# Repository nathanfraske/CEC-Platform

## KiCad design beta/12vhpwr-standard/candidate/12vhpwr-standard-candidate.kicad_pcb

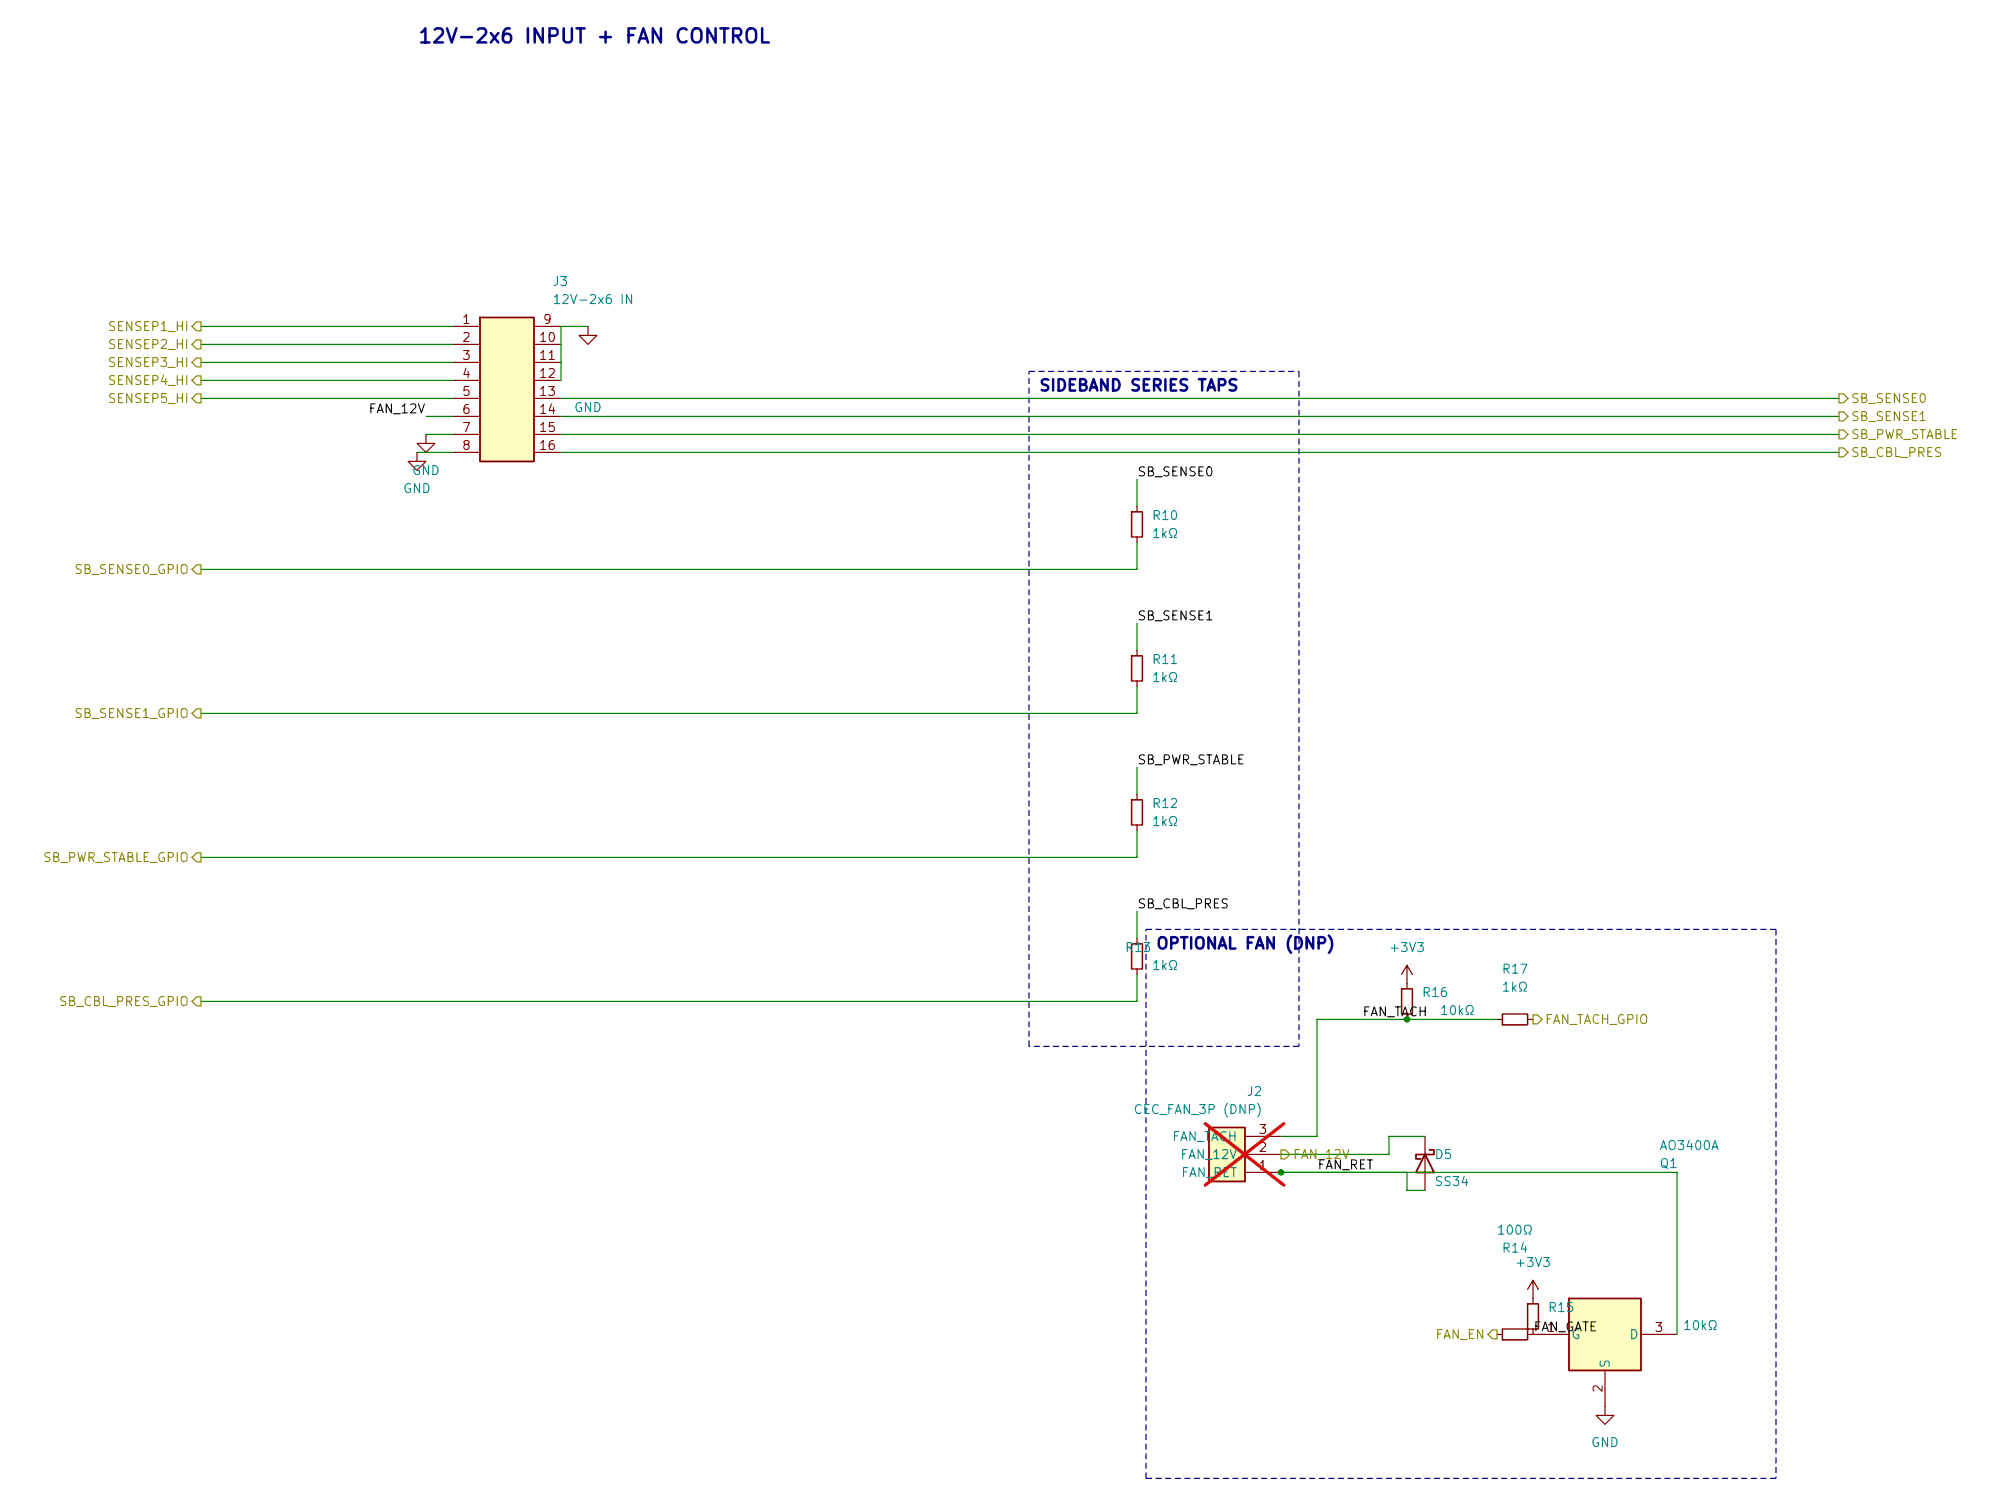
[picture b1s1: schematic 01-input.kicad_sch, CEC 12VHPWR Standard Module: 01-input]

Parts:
D5: SS34; D_SMA; MPN SS34; LCSC C8678
J2: CEC_FAN_3P (DNP); JST_PH_B3B-PH-K-S_1x03_P2.00mm_Vertical; MPN B3B-PH-K-S(LF)(SN); LCSC C131339; not fitted
J3: 12V-2x6 IN; CEC_12V2x6_Horizontal; MPN 2191161161; JLCPCB consigned (not in JLC catalog)
Q1: AO3400A; SOT-23-3_L2.9-W1.3-P1.90-LS2.4-BR; MPN AO3400A; LCSC C20917
R10, R11, R12, R13, R17: 1kΩ; R_0402_1005Metric; MPN 0402WGF1001TCE; LCSC C11702
R14: 100Ω; R_0402_1005Metric; MPN RC0402JR-07100RL; LCSC C106233
R15, R16: 10kΩ; R_0402_1005Metric; MPN 0402WGF1002TCE; LCSC C25744

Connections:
/FAN_12V: D5.1 (K), J2.2 (FAN_12V), J3.6 (+12V); also elsewhere on the board
/FAN_EN: R14.1; also elsewhere on the board
/SB_CBL_PRES: J3.16 (SENSE), R13.1; also elsewhere on the board
/SB_CBL_PRES_GPIO: R13.2; also elsewhere on the board
/SB_PWR_STABLE: J3.15 (SENSE), R12.1; also elsewhere on the board
/SB_PWR_STABLE_GPIO: R12.2; also elsewhere on the board
/SB_SENSE0: J3.13 (SENSE), R10.1; also elsewhere on the board
/SB_SENSE0_GPIO: R10.2; also elsewhere on the board
/SB_SENSE1: J3.14 (SENSE), R11.1; also elsewhere on the board
/SB_SENSE1_GPIO: R11.2; also elsewhere on the board
/SENSEP1_HI: J3.1 (+12V); also elsewhere on the board
/SENSEP2_HI: J3.2 (+12V); also elsewhere on the board
/SENSEP3_HI: J3.3 (+12V); also elsewhere on the board
/SENSEP4_HI: J3.4 (+12V); also elsewhere on the board
/SENSEP5_HI: J3.5 (+12V); also elsewhere on the board

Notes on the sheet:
12V-2x6 INPUT + FAN CONTROL
SIDEBAND SERIES TAPS
OPTIONAL FAN (DNP)

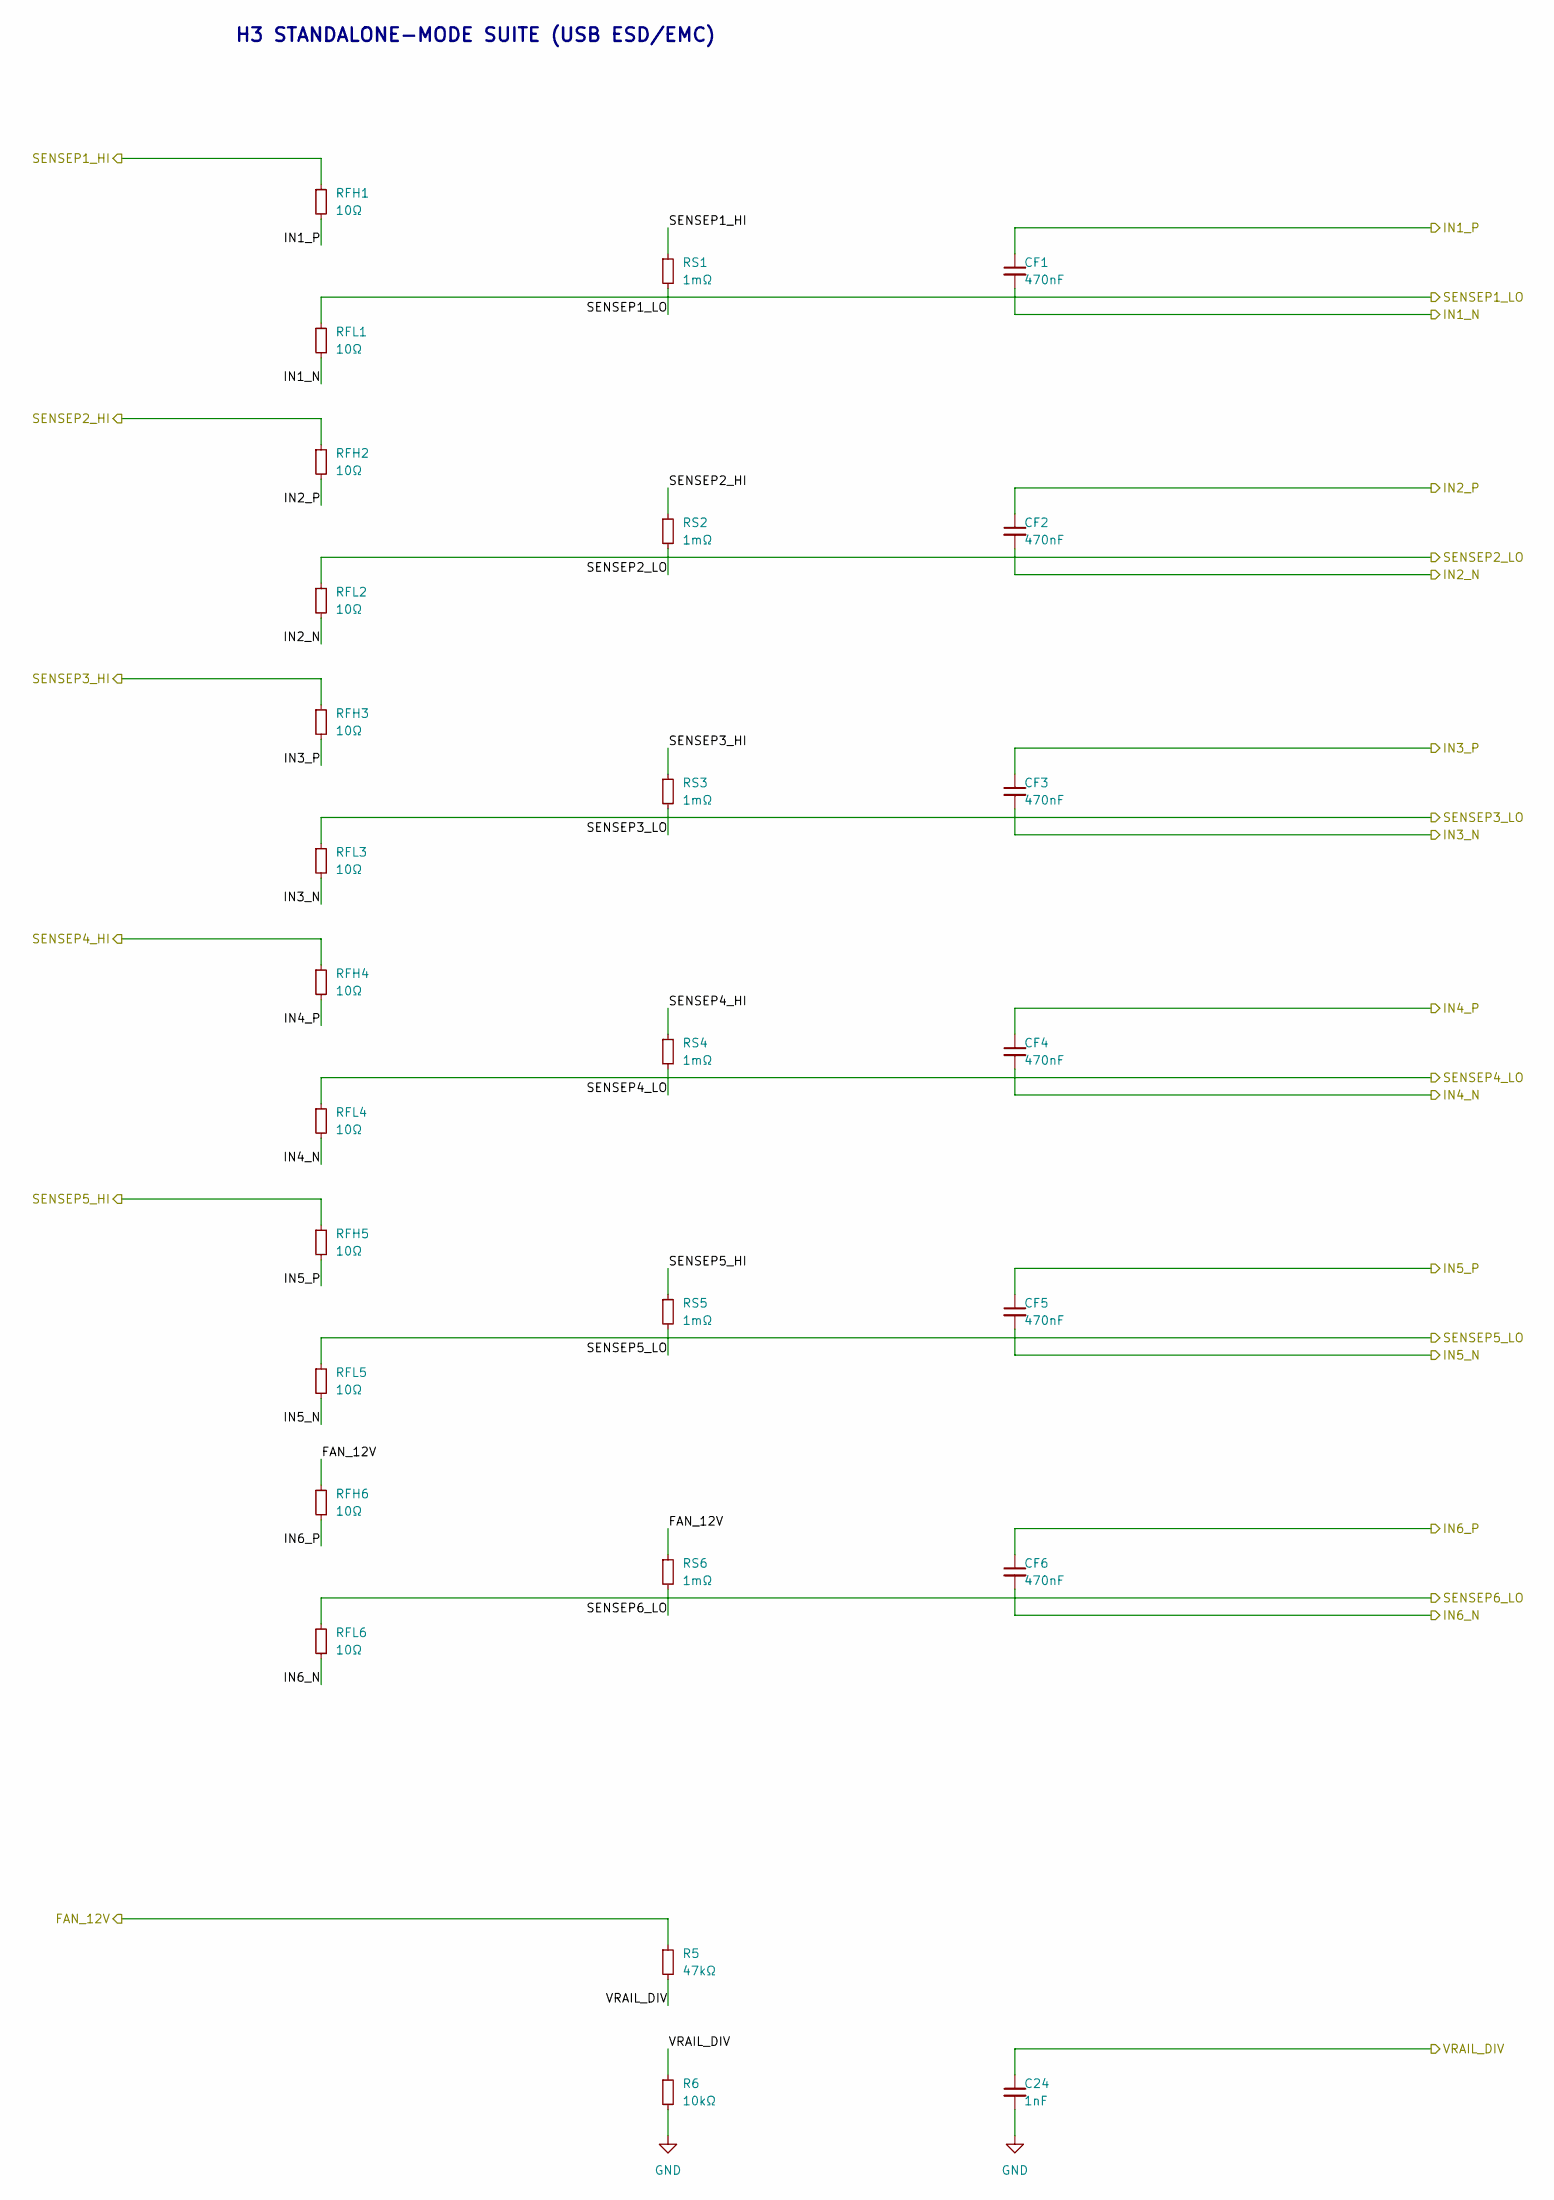
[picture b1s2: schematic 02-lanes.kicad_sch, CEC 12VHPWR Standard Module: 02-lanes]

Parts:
C24: 1nF; C_0402_1005Metric; MPN GRM1555C1H102JA01D; LCSC C76947
CF1, CF2, CF3, CF4, CF5, CF6: 470nF; C_0603_1608Metric; MPN CL10B474KA8NNNC; LCSC C1623
R5: 47kΩ; R_0402_1005Metric; Tolerance 0.1%; MPN RT0402BRD0747KL; LCSC C728561
R6: 10kΩ; R_0402_1005Metric; Tolerance 0.1%; MPN RT0402BRD0710KL; LCSC C190095
RFH1, RFH2, RFH3, RFH4, RFH5, RFH6: 10Ω; R_0402_1005Metric; Tolerance 0.1%; MPN RT0402BRE0710RL; LCSC C705642
RFL1, RFL2, RFL3, RFL4, RFL5, RFL6: 10Ω; R_0402_1005Metric; Tolerance 0.1%; MPN RT0402BRE0710RL; LCSC C705642
RS1, RS2, RS3, RS4, RS5, RS6: 1mΩ; R_2512_6332Metric; MPN CSS2H-2512R-1L00F; LCSC C4175647

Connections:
/FAN_12V: R5.1, RFH6.1, RS6.1; also elsewhere on the board
/IN1_N: CF1.2, RFL1.2; also elsewhere on the board
/IN1_P: CF1.1, RFH1.2; also elsewhere on the board
/IN2_N: CF2.2, RFL2.2; also elsewhere on the board
/IN2_P: CF2.1, RFH2.2; also elsewhere on the board
/IN3_N: CF3.2, RFL3.2; also elsewhere on the board
/IN3_P: CF3.1, RFH3.2; also elsewhere on the board
/IN4_N: CF4.2, RFL4.2; also elsewhere on the board
/IN4_P: CF4.1, RFH4.2; also elsewhere on the board
/IN5_N: CF5.2, RFL5.2; also elsewhere on the board
/IN5_P: CF5.1, RFH5.2; also elsewhere on the board
/IN6_N: CF6.2, RFL6.2; also elsewhere on the board
/IN6_P: CF6.1, RFH6.2; also elsewhere on the board
/SENSEP1_HI: RFH1.1, RS1.1; also elsewhere on the board
/SENSEP1_LO: RFL1.1, RS1.2; also elsewhere on the board
/SENSEP2_HI: RFH2.1, RS2.1; also elsewhere on the board
/SENSEP2_LO: RFL2.1, RS2.2; also elsewhere on the board
/SENSEP3_HI: RFH3.1, RS3.1; also elsewhere on the board
/SENSEP3_LO: RFL3.1, RS3.2; also elsewhere on the board
/SENSEP4_HI: RFH4.1, RS4.1; also elsewhere on the board
/SENSEP4_LO: RFL4.1, RS4.2; also elsewhere on the board
/SENSEP5_HI: RFH5.1, RS5.1; also elsewhere on the board
/SENSEP5_LO: RFL5.1, RS5.2; also elsewhere on the board
/SENSEP6_LO: RFL6.1, RS6.2; also elsewhere on the board
/VRAIL_DIV: C24.1, R5.2, R6.1; also elsewhere on the board

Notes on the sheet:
H3 STANDALONE-MODE SUITE (USB ESD/EMC)

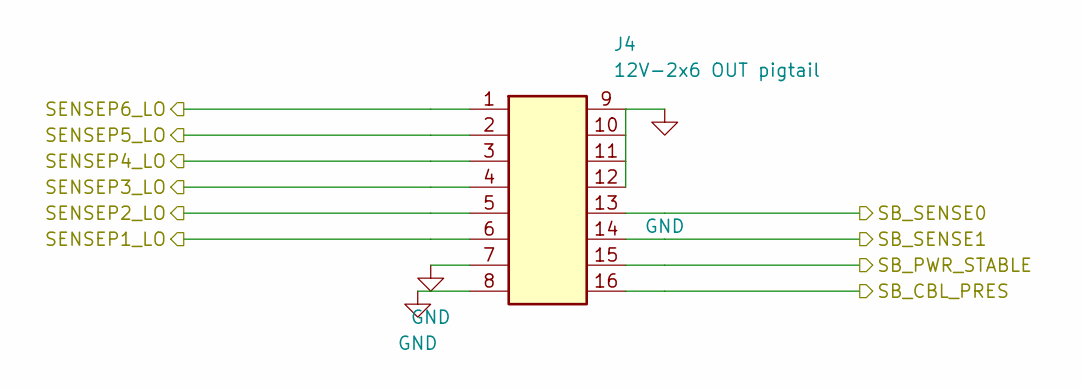
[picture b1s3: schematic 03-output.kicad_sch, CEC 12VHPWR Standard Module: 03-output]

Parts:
J4: 12V-2x6 OUT pigtail; CEC_12V2x6_Horizontal; MPN 2191161161; JLCPCB consigned (not in JLC catalog)

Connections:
/SB_CBL_PRES: J4.16 (SENSE); also elsewhere on the board
/SB_PWR_STABLE: J4.15 (SENSE); also elsewhere on the board
/SB_SENSE0: J4.13 (SENSE); also elsewhere on the board
/SB_SENSE1: J4.14 (SENSE); also elsewhere on the board
/SENSEP1_LO: J4.6 (+12V); also elsewhere on the board
/SENSEP2_LO: J4.5 (+12V); also elsewhere on the board
/SENSEP3_LO: J4.4 (+12V); also elsewhere on the board
/SENSEP4_LO: J4.3 (+12V); also elsewhere on the board
/SENSEP5_LO: J4.2 (+12V); also elsewhere on the board
/SENSEP6_LO: J4.1 (+12V); also elsewhere on the board

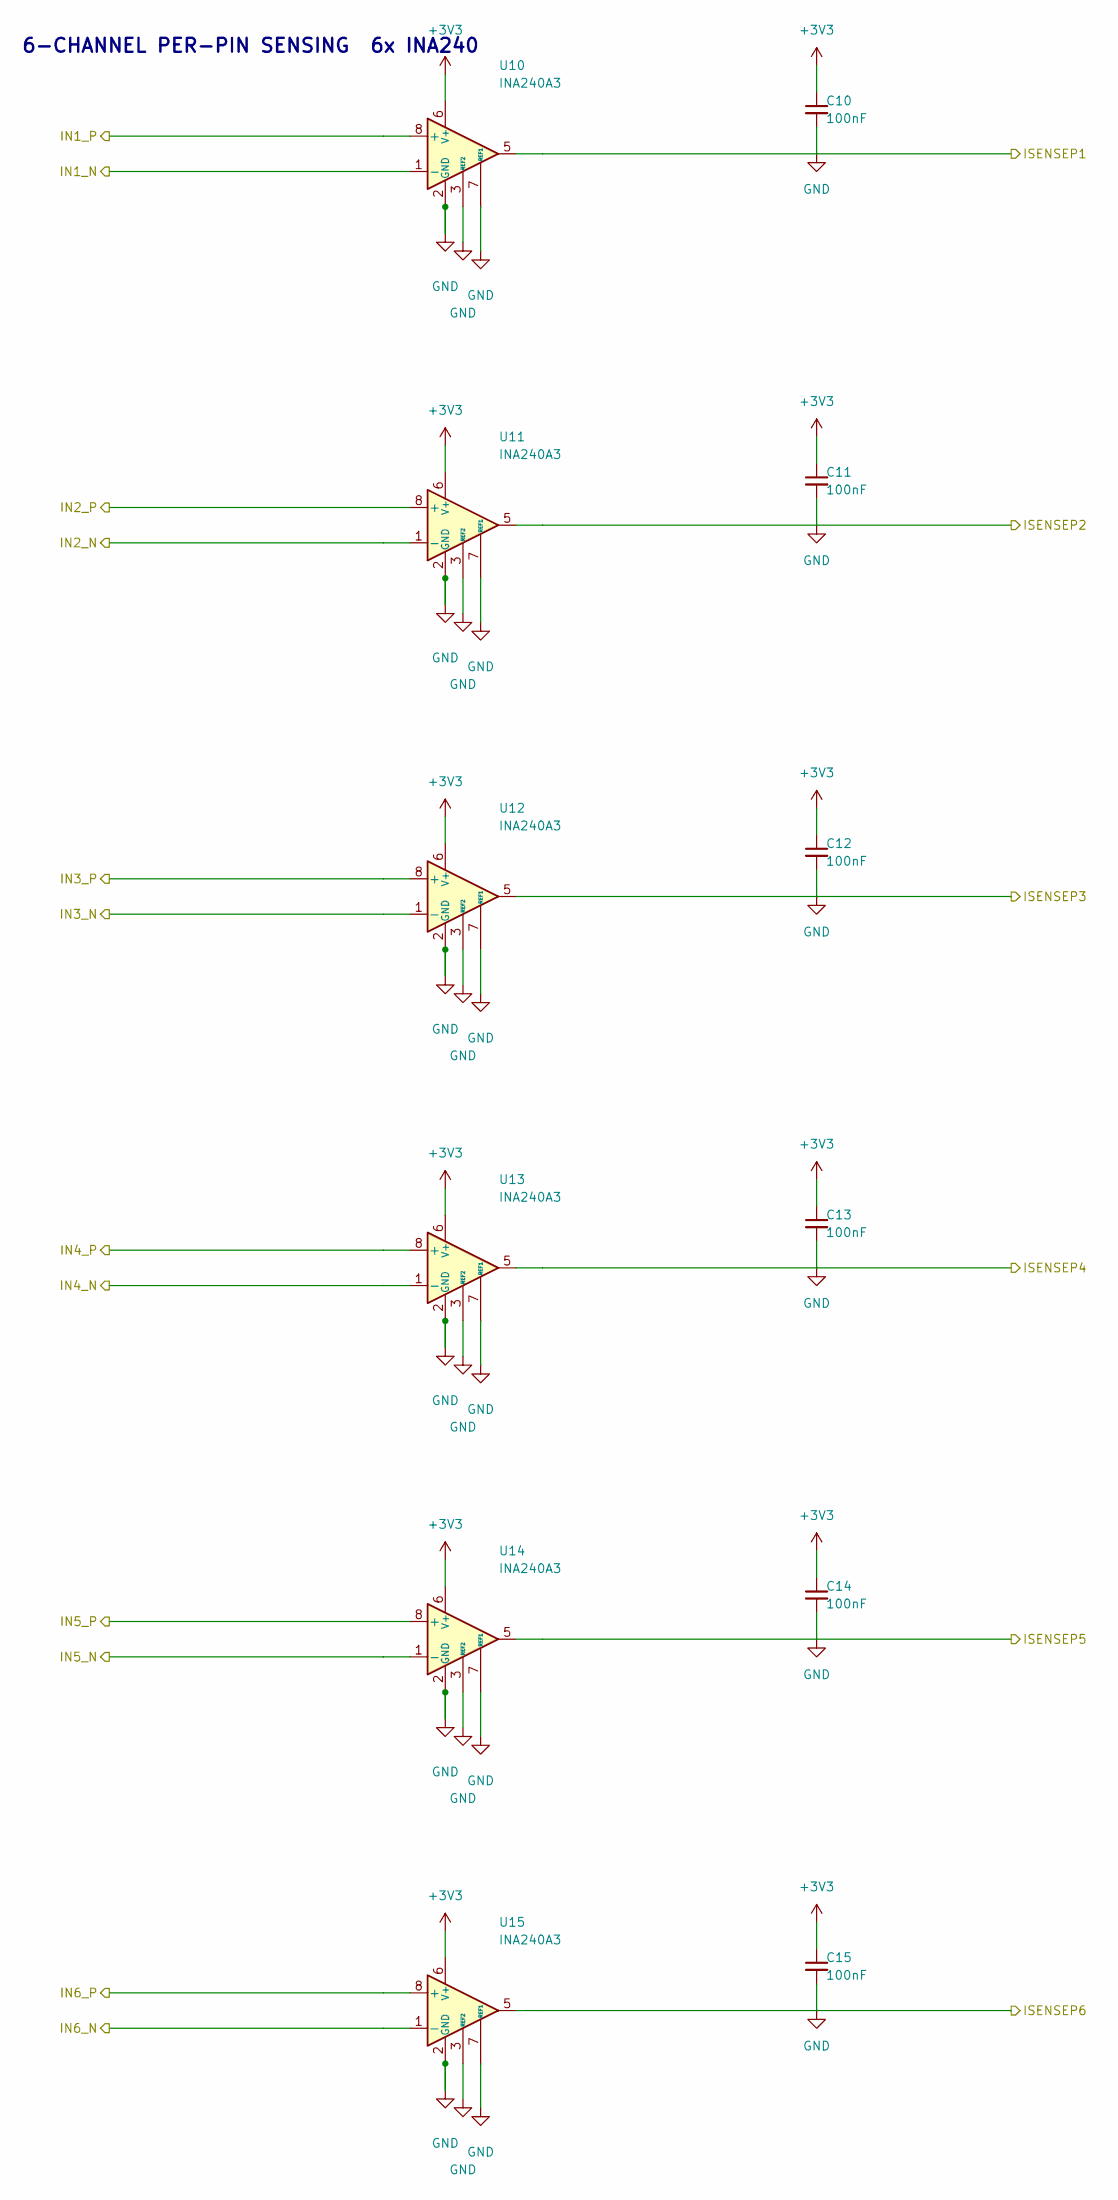
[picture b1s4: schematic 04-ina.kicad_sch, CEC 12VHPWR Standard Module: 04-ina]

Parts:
C10, C11, C12, C13, C14, C15: 100nF; C_0402_1005Metric; MPN CL05B104KO5NNNC; LCSC C1525
U10, U11, U12, U13, U14, U15: INA240A3; SOIC-8_3.9x4.9mm_P1.27mm; MPN INA240A3DR; LCSC C2060584

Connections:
/IN1_N: U10.1 (-); also elsewhere on the board
/IN1_P: U10.8 (+); also elsewhere on the board
/IN2_N: U11.1 (-); also elsewhere on the board
/IN2_P: U11.8 (+); also elsewhere on the board
/IN3_N: U12.1 (-); also elsewhere on the board
/IN3_P: U12.8 (+); also elsewhere on the board
/IN4_N: U13.1 (-); also elsewhere on the board
/IN4_P: U13.8 (+); also elsewhere on the board
/IN5_N: U14.1 (-); also elsewhere on the board
/IN5_P: U14.8 (+); also elsewhere on the board
/IN6_N: U15.1 (-); also elsewhere on the board
/IN6_P: U15.8 (+); also elsewhere on the board

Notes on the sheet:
6-CHANNEL PER-PIN SENSING 6x INA240

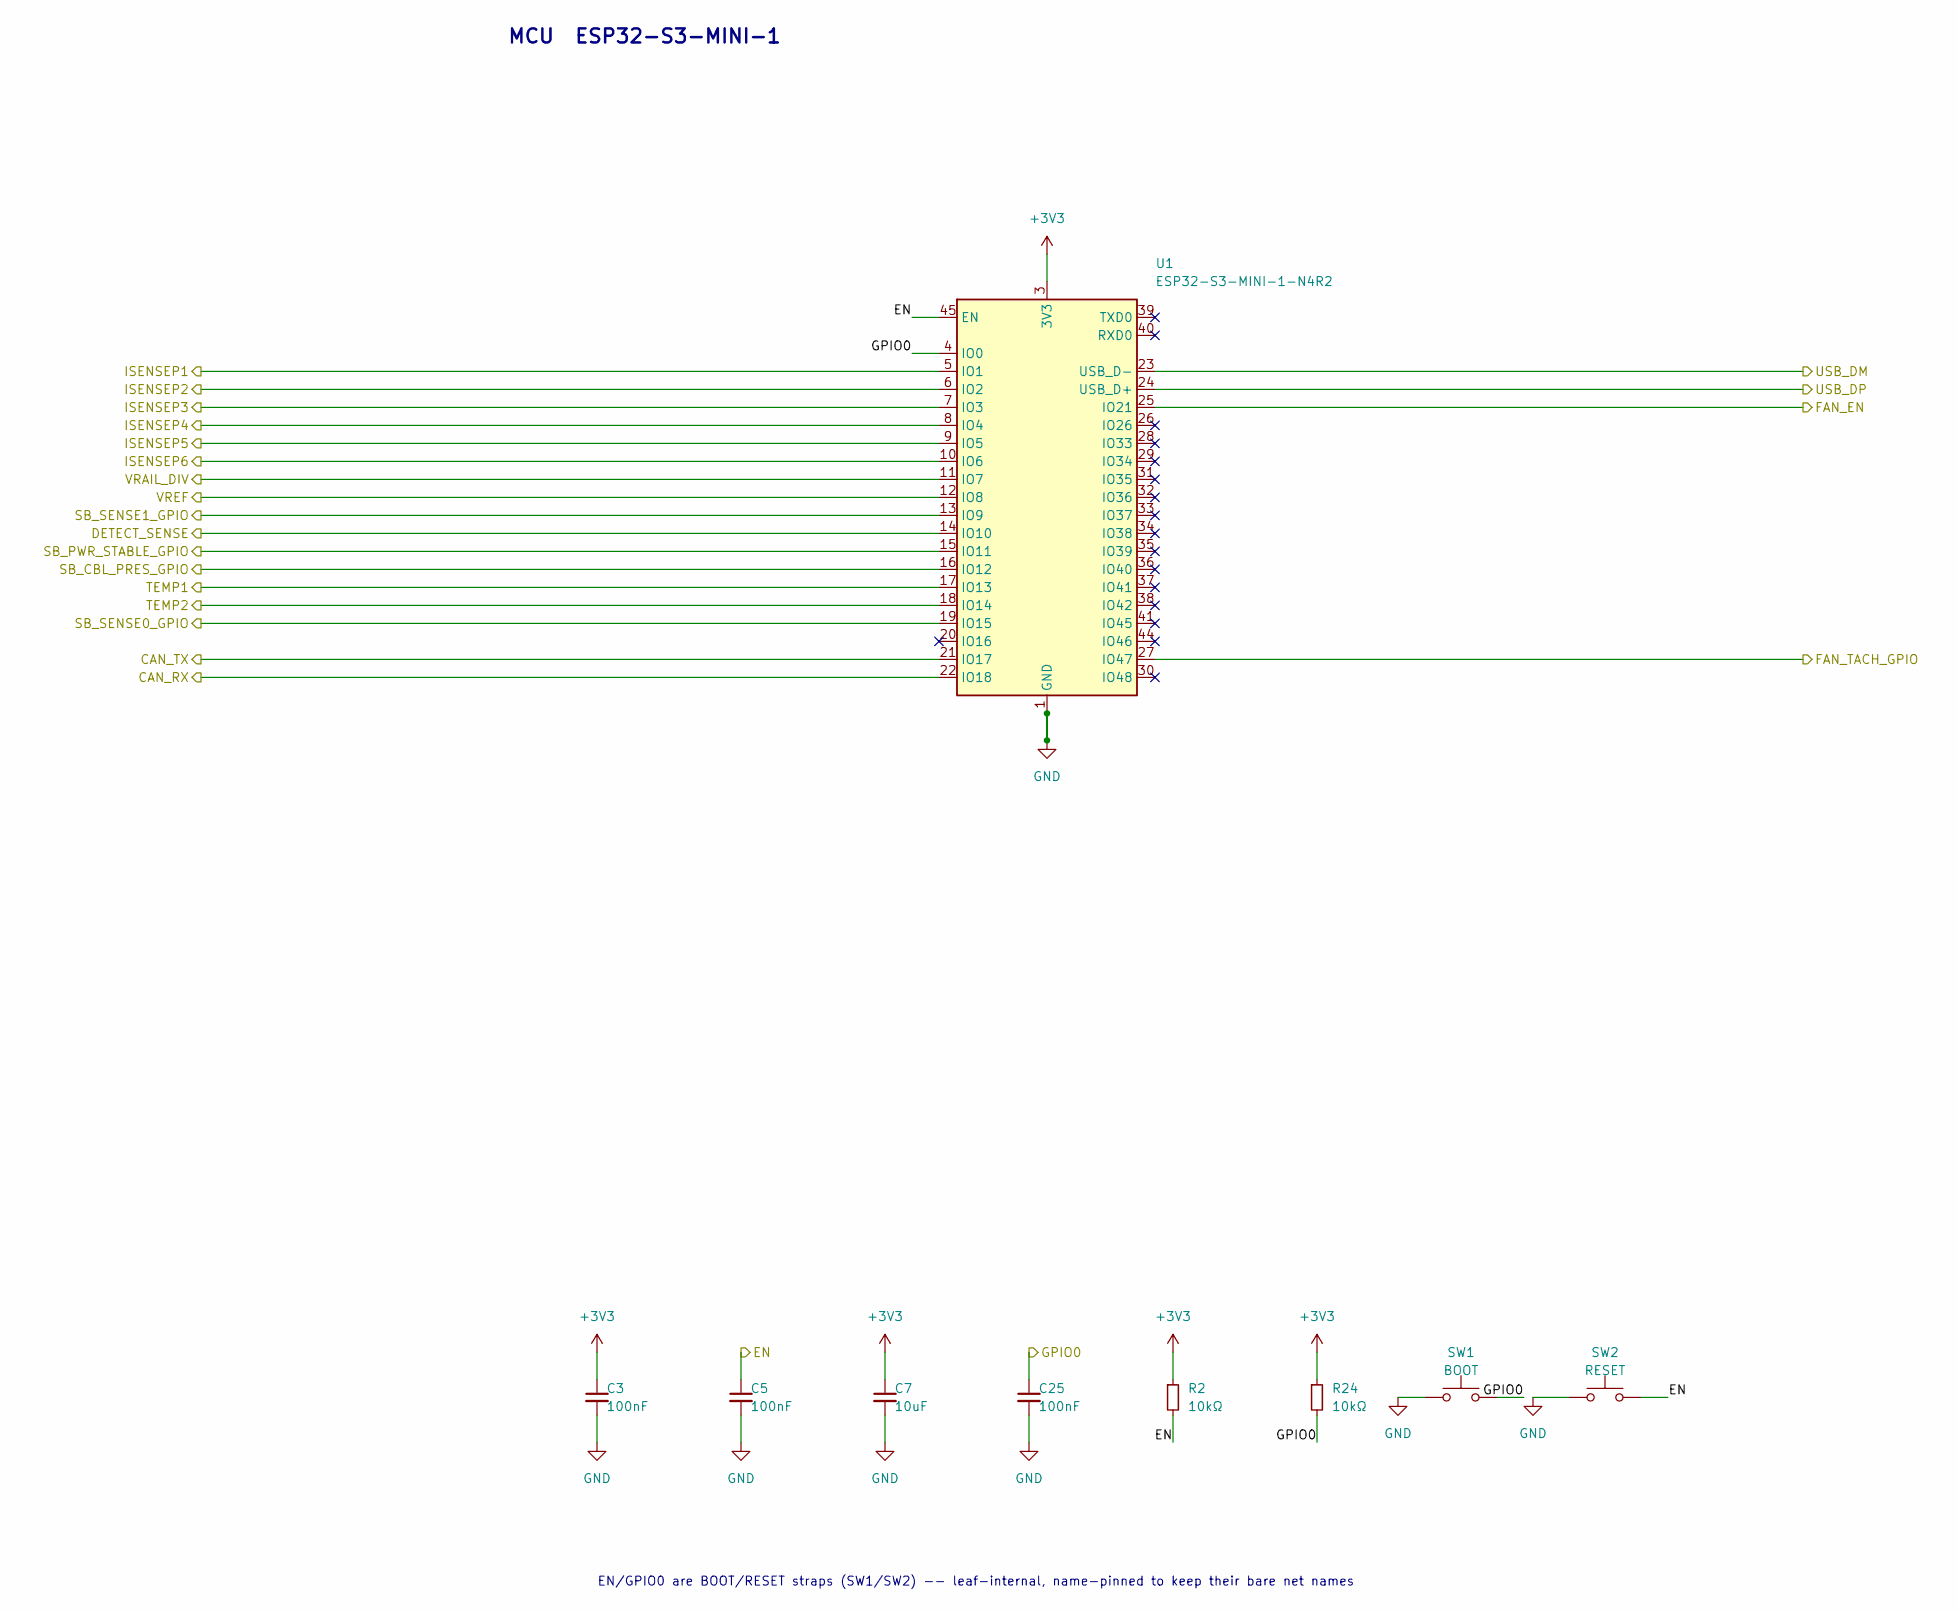
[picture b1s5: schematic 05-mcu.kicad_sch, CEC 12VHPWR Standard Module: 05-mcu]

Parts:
C3, C5, C25: 100nF; C_0402_1005Metric; MPN CL05B104KO5NNNC; LCSC C1525
C7: 10uF; C_0805_2012Metric; MPN CL21A106KAYNNNE; LCSC C15850
R2, R24: 10kΩ; R_0402_1005Metric; MPN 0402WGF1002TCE; LCSC C25744
SW1: BOOT; TS-1088-AR02016; MPN TS-1088-AR02016; LCSC C720477
SW2: RESET; TS-1088-AR02016; MPN TS-1088-AR02016; LCSC C720477
U1: ESP32-S3-MINI-1-N4R2; ESP32-S2-MINI-1_NoAntKeepout; MPN ESP32-S3-MINI-1-N4R2; LCSC C3013941

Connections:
/CAN_RX: U1.22 (IO18); also elsewhere on the board
/CAN_TX: U1.21 (IO17); also elsewhere on the board
/EN: C5.1, R2.2, SW2.2, U1.45 (EN)
/FAN_EN: U1.25 (IO21); also elsewhere on the board
/GPIO0: C25.1, R24.2, SW1.2, U1.4 (IO0)
/SB_CBL_PRES_GPIO: U1.16 (IO12); also elsewhere on the board
/SB_PWR_STABLE_GPIO: U1.15 (IO11); also elsewhere on the board
/SB_SENSE0_GPIO: U1.19 (IO15); also elsewhere on the board
/SB_SENSE1_GPIO: U1.13 (IO9); also elsewhere on the board
/TEMP1: U1.17 (IO13); also elsewhere on the board
/TEMP2: U1.18 (IO14); also elsewhere on the board
/USB_DM: U1.23 (USB_D-); also elsewhere on the board
/USB_DP: U1.24 (USB_D+); also elsewhere on the board
/VRAIL_DIV: U1.11 (IO7); also elsewhere on the board
/VREF: U1.12 (IO8); also elsewhere on the board

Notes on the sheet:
MCU ESP32-S3-MINI-1
EN/GPIO0 are BOOT/RESET straps (SW1/SW2) -- leaf-internal, name-pinned to keep their bare net names

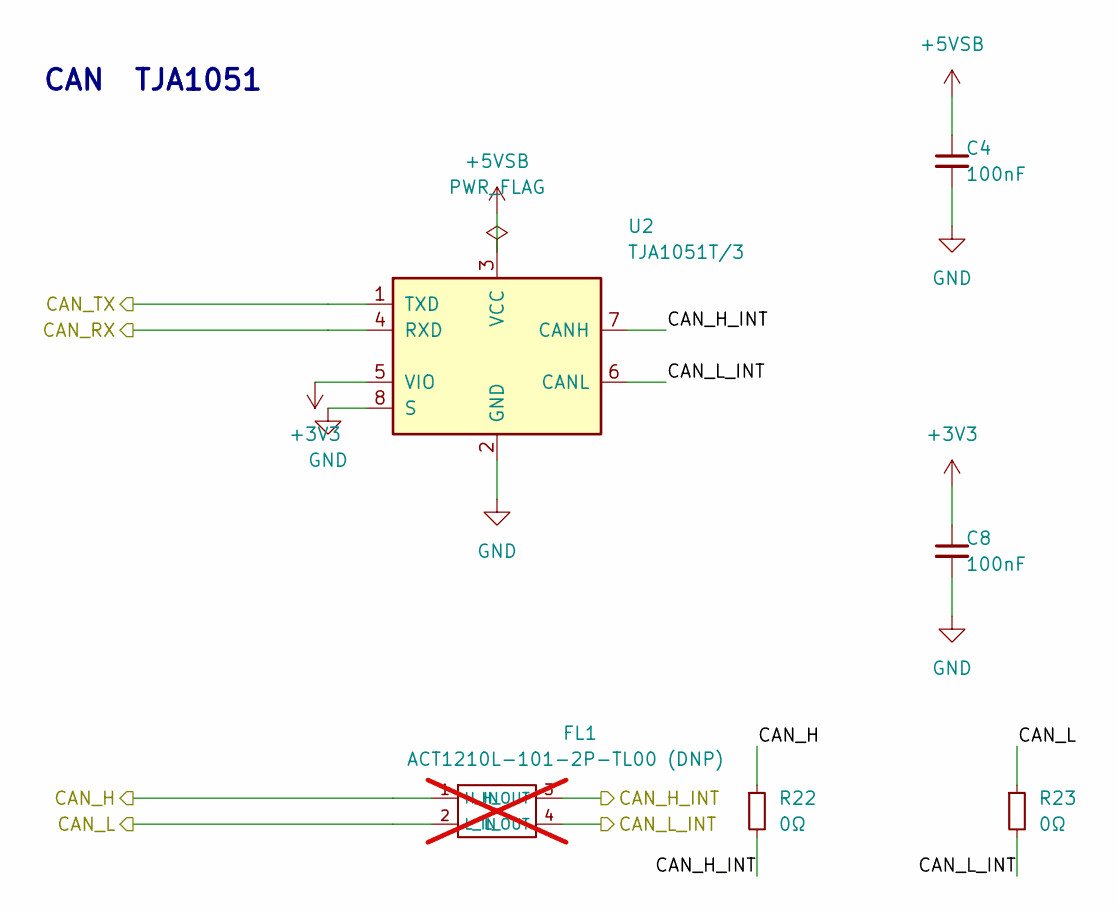
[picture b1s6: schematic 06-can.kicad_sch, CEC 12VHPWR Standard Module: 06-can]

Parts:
C4, C8: 100nF; C_0402_1005Metric; MPN CL05B104KO5NNNC; LCSC C1525
FL1: ACT1210L-101-2P-TL00 (DNP); MPN ACT1210L-101-2P-TL00; LCSC C307643; not fitted
R22, R23: 0Ω; R_0402_1005Metric; MPN 0402WGF0000TCE; LCSC C17168
U2: TJA1051T/3; SOIC-8_3.9x4.9mm_P1.27mm; MPN TJA1051T/3/1J; LCSC C38695

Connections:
+5VSB: C4.1, U2.3 (VCC); also elsewhere on the board
/CAN_H: R22.1; also elsewhere on the board
/CAN_H_INT: R22.2, U2.7 (CANH)
/CAN_L: R23.1; also elsewhere on the board
/CAN_L_INT: R23.2, U2.6 (CANL)
/CAN_RX: U2.4 (RXD); also elsewhere on the board
/CAN_TX: U2.1 (TXD); also elsewhere on the board

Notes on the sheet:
CAN TJA1051

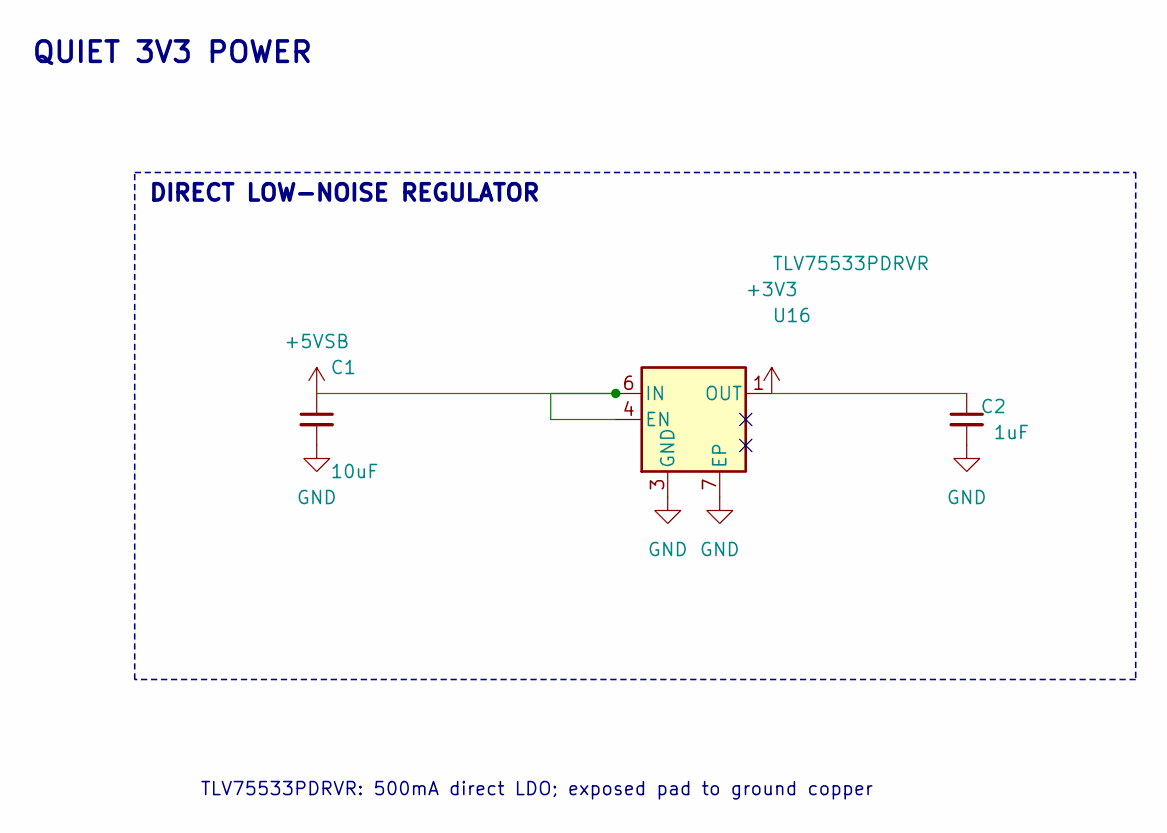
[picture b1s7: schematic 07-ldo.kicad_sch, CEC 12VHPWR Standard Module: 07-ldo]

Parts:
C1: 10uF; C_0603_1608Metric; MPN CL10A106MA8NRNC; LCSC C96446
C2: 1uF; C_0603_1608Metric; MPN CL10B105KA8NNNC; LCSC C29936
U16: TLV75533PDRVR; WSON-6-1EP_2x2mm_P0.65mm_EP1x1.6mm; MPN TLV75533PDRVR; LCSC C2861750

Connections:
+5VSB: C1.1, U16.4 (EN), U16.6 (IN); also elsewhere on the board

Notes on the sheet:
QUIET 3V3 POWER
TLV75533PDRVR: 500mA direct LDO; exposed pad to ground copper
DIRECT LOW-NOISE REGULATOR

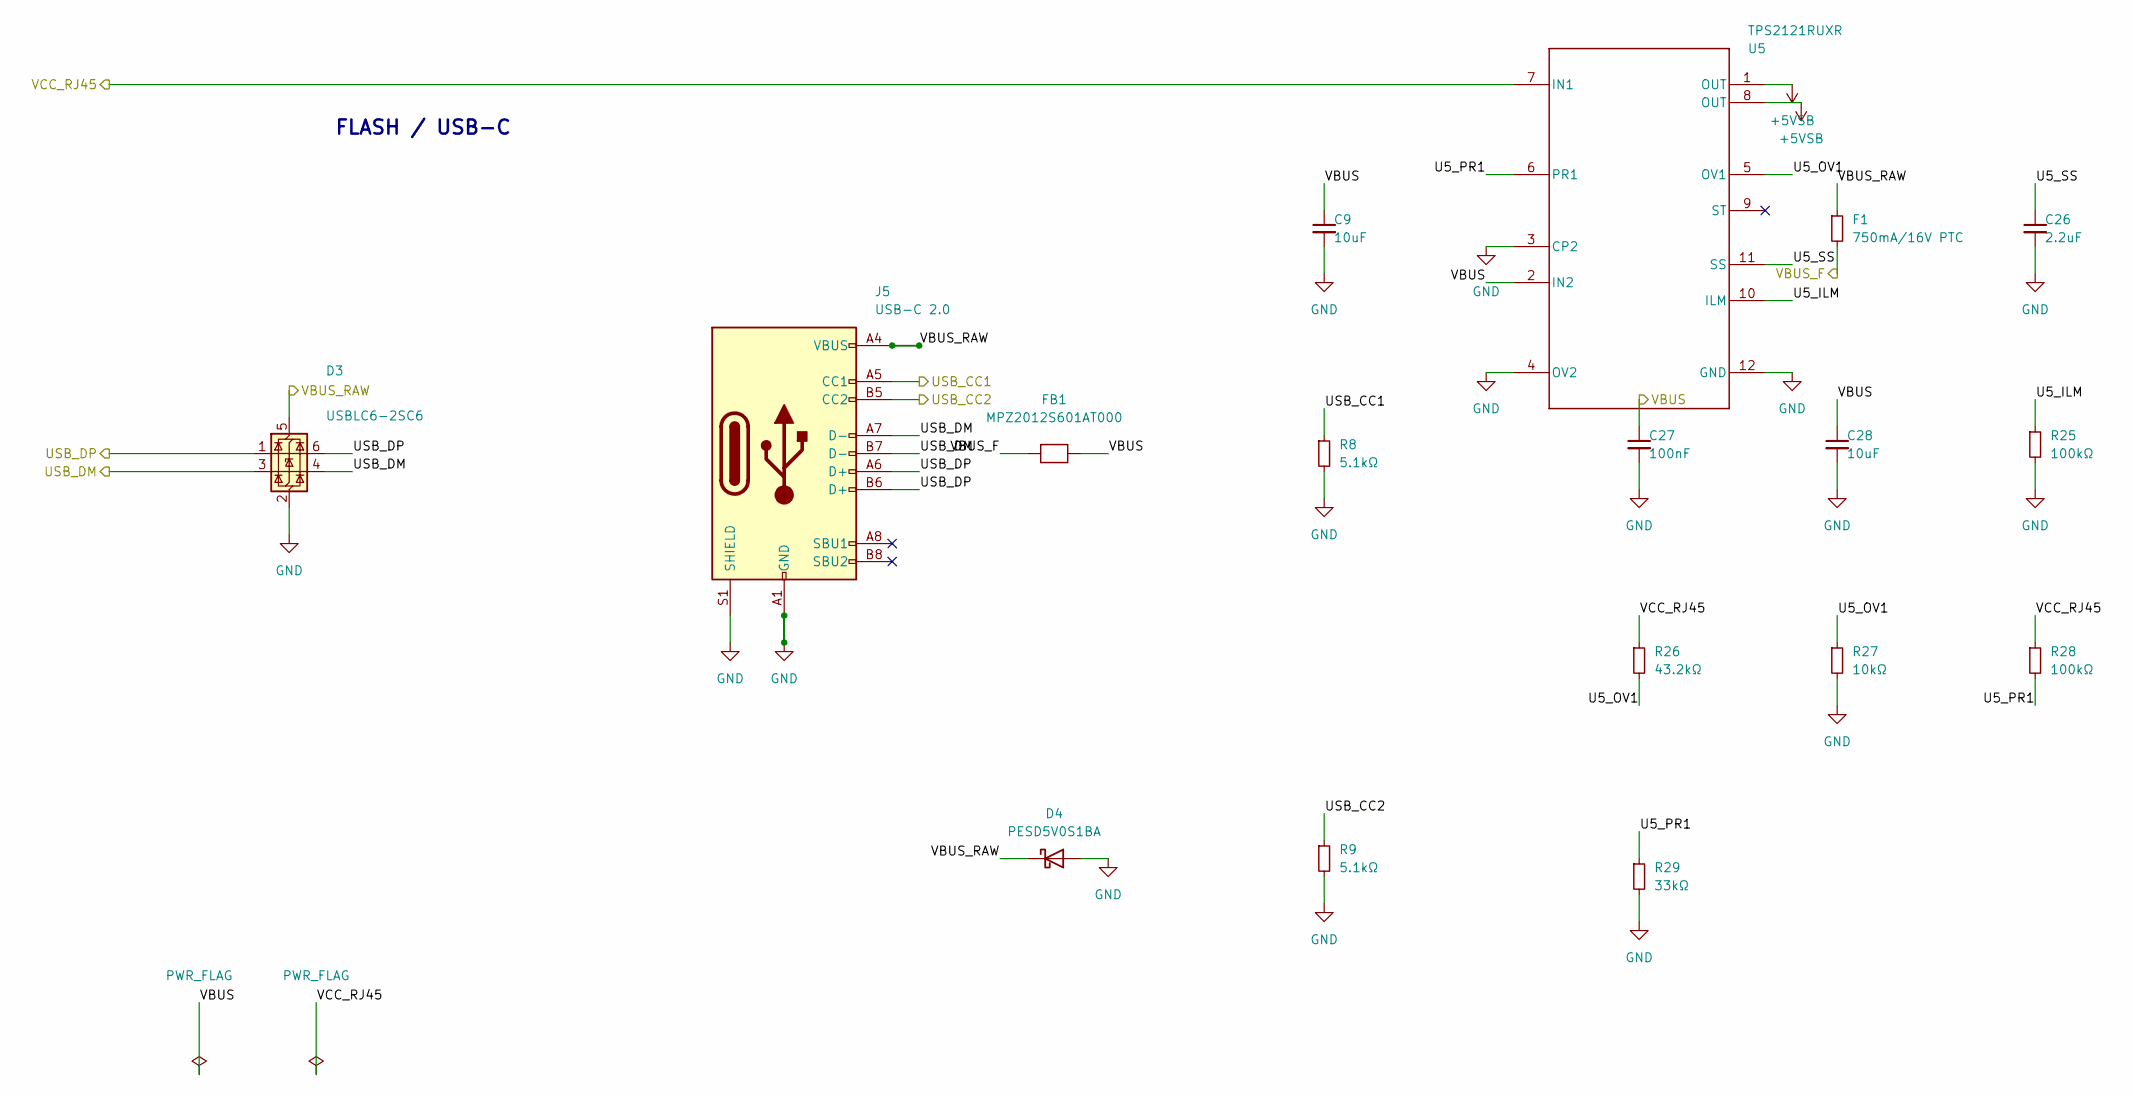
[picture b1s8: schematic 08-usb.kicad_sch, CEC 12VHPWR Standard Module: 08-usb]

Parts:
C9, C28: 10uF; C_0805_2012Metric; MPN CL21A106KAYNNNE; LCSC C15850
C26: 2.2uF; C_0603_1608Metric; MPN CL10A225KO8NNNC; LCSC C23630
C27: 100nF; C_0402_1005Metric; MPN CL05B104KO5NNNC; LCSC C1525
D3: USBLC6-2SC6; SOT-23-6; MPN USBLC6-2SC6; LCSC C2687116
D4: PESD5V0S1BA; D_SOD-323; MPN PESD5V0S1BA; LCSC C5261083
F1: 750mA/16V PTC; R_1206_3216Metric; MPN 1206L075/16WR; LCSC C371166
FB1: MPZ2012S601AT000; C_0805_2012Metric; MPN MPZ2012S601AT000; LCSC C21519
J5: USB-C 2.0; USB_C_Receptacle_XKB_U262-16XN-4BVC11; MPN U262-161N-4BVC11; LCSC C319148
R8, R9: 5.1kΩ; R_0402_1005Metric; MPN 0402WGF5101TCE; LCSC C25905
R25, R28: 100kΩ; R_0402_1005Metric; MPN 0402WGF1003TCE; LCSC C25741
R26: 43.2kΩ; R_0402_1005Metric; MPN 0402WGF4322TCE; LCSC C25894
R27: 10kΩ; R_0402_1005Metric; MPN 0402WGF1002TCE; LCSC C25744
R29: 33kΩ; R_0402_1005Metric; MPN 0402WGF3302TCE; LCSC C25779
U5: TPS2121RUXR; RUX0012A; MPN TPS2121RUXR; LCSC C485916

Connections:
+5VSB: U5.1 (OUT), U5.8 (OUT); also elsewhere on the board
/08-usb/U5_ILM: R25.1, U5.10 (ILM)
/08-usb/U5_OV1: R26.2, R27.1, U5.5 (OV1)
/08-usb/U5_PR1: R28.2, R29.1, U5.6 (PR1)
/08-usb/U5_SS: C26.1, U5.11 (SS)
/USB_CC1: J5.A5 (CC1), R8.1
/USB_CC2: J5.B5 (CC2), R9.1
/USB_DM: D3.3 (I/O2), D3.4 (I/O2), J5.A7 (D-), J5.B7 (D-); also elsewhere on the board
/USB_DP: D3.1 (I/O1), D3.6 (I/O1), J5.A6 (D+), J5.B6 (D+); also elsewhere on the board
/VBUS: C9.1, C27.1, C28.1, FB1.2, U5.2 (IN2)
/VBUS_F: F1.2, FB1.1
/VBUS_RAW: D3.5 (VBUS), D4.1 (K), F1.1, J5.A4 (VBUS), J5.A9 (VBUS), J5.B4 (VBUS), J5.B9 (VBUS)
/VCC_RJ45: R26.1, R28.1, U5.7 (IN1); also elsewhere on the board

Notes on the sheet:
FLASH / USB-C

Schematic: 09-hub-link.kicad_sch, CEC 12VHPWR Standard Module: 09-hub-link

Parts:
C6: 10uF; C_0805_2012Metric; MPN CL21A106KAYNNNE; LCSC C15850
D1: PESD5V0S1BA; D_SOD-323; MPN PESD5V0S1BA; LCSC C5261083
FB2: 0R; C_0805_2012Metric; MPN 0805W8F0000T5E; LCSC C17477
J1: TO-HUB; RJ45_FTP_Shielded_Horizontal; MPN KH-RJ45-58-8P8C; LCSC C2683360
R1: 2.2kΩ; R_0402_1005Metric; MPN 0402WGF2201TCE; LCSC C25879
R7: 100kΩ; R_0402_1005Metric; MPN 0402WGF1003TCE; LCSC C25741

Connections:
/CAN_H: J1.3 (CAN1_H); also elsewhere on the board
/CAN_L: J1.6 (CAN1_L); also elsewhere on the board
/DETECT: D1.1 (K), J1.8 (DETECT), R1.1, R7.1
/VCC_RAW: FB2.2, J1.1 (VCC)
/VCC_RJ45: C6.1, FB2.1; also elsewhere on the board

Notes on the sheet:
HUB LINK RJ-45 + DETECT

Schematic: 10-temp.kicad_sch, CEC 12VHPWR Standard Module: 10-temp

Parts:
C20, C21: 100nF; C_0402_1005Metric; MPN CL05B104KO5NNNC; LCSC C1525
R20, R21: 10kΩ; R_0402_1005Metric; MPN 0402WGF1002TCE; LCSC C25744
TH1, TH2: NTC 10k; NTC_0402_1005Metric; MPN NCP15XH103F03RC; LCSC C77131

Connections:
/TEMP1: C20.1, R20.1, TH1.2; also elsewhere on the board
/TEMP2: C21.1, R21.1, TH2.2; also elsewhere on the board
